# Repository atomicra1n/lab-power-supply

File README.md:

# Lab Power Supply

An adjustable power supply powered by a laptop charger. Features knobs for changing the voltage and current limit, voltage and ampere meter, button to show the current limit on the meter. The circuit is fully analog and features no firmware or microcontroller.

## Features

- Customizable output from 1.25V to about 16.5 volts. 
- Customizable current limit from 0 ampers to about 2.2 ampers.
- Red LED that lights up when the supply is limiting.
- Meter that shows the output voltage and current.
- OUTPUT switch for toggling the outputs.
- SHOW LIMIT button that shows the current limit instead of the voltage on the display.
- Reverse polarity protection.
- Resettable fuse on the input
- Undervoltage lockout
- Runs off a standard 19V laptop charger w/ a 5.5/2.5mm jack.
- Fully THT, no complicated SMD soldering.
- 3D printed enclosure with vents for heat, tilted feet and knobs.

## Motivation

Thinking about what I was going to make for week 5, I wanted something that would be genuinely useful for my future tinkering. Recently, I was reverse engineering a Cisco switch and needed a source of 3.3V. Thankfully, my Raspberry Pi Pico was able to deliver enough, but it was close to not being enough. This would be a good solution for the future!

## Functionality

- The laptop charger plugs into a DC jack on the back of the enclosure. This is wired to a screw terminal on the PCB. Power goes through a resettable fuse and a P-MOSFET for reverse polarity protection.
- An LM2576T-ADJ steps the voltage down. There are two 1k parallel resistors and a 10k potentiometer (VOLTAGE) for the feedback divider.
- A TL431 makes a 2.495 volt reference and one LM324 compares it with a third of the input voltage. If it goes below about 6.8V, the regulator turns off. Above about 8.8V, it turns back on (with hysteresis). This fulfills undervoltage lockout.
- An 0.1 ohm shunt resistor sits in the output's negative path for current sensing. An op-amp amplifies its voltage 11 times.
- A second op-amp compares that with the setting of the CURRENT knob. If the current is too high, current enters the LM2576 feedback pin through the red LED and a 1k resistor, which forces the regulator to lower output. The LED also blocks current from flowing back.
- The SHOW LIMIT button uses a third op-amp to switch the meter's voltage wire between the output and the current limit signal.
- Made only out of 1k/10k resistors to save costs as my local electronics shop has minimum order quantities on each.

## How it was made

All electrical work was done in KiCad and all CAD work was done in Autodesk Fusion. I ran into some issues:

- Originally I planned to use a TL431 to drive the LM2576's ON/OFF pins directly, but the datasheet of the LM2576 says the pin has to go below about 1V to turn it on. However, a TL431 can't get its output below about 2V, so the regulator might never turn on. I switched the LM358 for a LM324 which was even cheaper.
- I had 1k resistor for the green power LED but it is only rated for 7mA, which would come out to about 17 mA at 18V. I added 2 more 1K resistors in series.
- I wired the CURRENT potentiometer backwards which would mean turning it clockwise would lower the limit.
- When routing, I first connected the current sensing input inefficiently which would increase resistance and make the current limit kick in too early.
- The ground pour didn't reach all pads so I needed to add some vias and tracks.
- In Fusion, I often swapped axis and built the tray on the wrong side of the components.

## Tech stack

- KiCad for the schematic and PCB
- Autodesk Fusion for the enclosure and knobs
- JLCPCB for the board, GM Electronic for the parts

## Repo layout

- pcb/ contains all KiCad work, including the project, PCB, footprints and schematic
- pcb/gerbers contains gerber, drill files and a zip file for the gerbers.
- cad/ contains the Fusion files and STEP files
- stl/ contains the printable parts
- images/ contains renders and screenshots

## Bill of materials

| Part | Qty | Source | Unit | Total |
|---|---|---|---|---|
| [PCB Manufacturing (5 pcs)](https://jlcpcb.com) | 1 | JLCPCB | $4.00 | $4.00 |
| [TAEJIN-HTC LM2576T-ADJ regulator](https://www.gme.cz/v/1519044/taejin-htc-korea-lm2576t-adj-vykonovy-spinany-regulatorstep-down) | 1 | GM Electronic | $2.31 | $2.31 |
| [TALEMA DPO-3.0-100 inductor](https://www.gme.cz/v/1494058/talema-dpo-30-100-tlumivka) | 1 | GM Electronic | $3.07 | $3.07 |
| [SB540 Schottky diode](https://www.gme.cz/v/1514436/sb540-yj-schottkyho-dioda) | 2 | GM Electronic | $0.45 | $0.90 |
| [V7143 heatsink](https://www.gme.cz/v/1499787/v7143-black-chladic) | 1 | GM Electronic | $1.56 | $1.56 |
| [Infineon IRF9540N MOSFET](https://www.gme.cz/v/1493222/infineon-irf9540npbf-unipolarni-tranzistor) | 1 | GM Electronic | $0.61 | $0.61 |
| [TL431ACZ reference](https://www.gme.cz/v/1493687/tl431acz) | 1 | GM Electronic | $0.28 | $0.28 |
| [Capacitor 470 microFarad 35V](https://www.gme.cz/v/1486880/hitano-ce-470u-35v-hit-ecr-10x16-rm5-bulk-elektrolyticky-kondenzator) | 5 | GM Electronic | $0.18 | $0.90 |
| [Capacitor 100 nanoFarad](https://www.gme.cz/v/1520318/ck-100n-50v-x7r-rm508-10-keramicky-kondenzator) | 8 | GM Electronic | $0.09 | $0.72 |
| [Resistor 1 kiloohm 0207](https://www.gme.cz/v/1486228/gym-cym-rm-1k-06w-1-0207-metalizovany-rezistor) | 10 | GM Electronic | $0.09 | $0.90 |
| [Resistor 10 kiloohm 0207](https://www.gme.cz/v/1494150/gym-cym-rm-10k-06w-1-0207-metalizovany-rezistor) | 10 | GM Electronic | $0.09 | $0.90 |
| [Shunt resistor 0.1 ohm 3W](https://www.gme.cz/v/1486965/hitano-rd-0r1-3w-5-0617-dratovy-rezistor) | 4 | GM Electronic | $0.22 | $0.88 |
| [Texas Instruments LM324N op-amp](https://www.gme.cz/v/1490186/texas-instruments-lm324n) | 1 | GM Electronic | $0.42 | $0.42 |
| [10 kiloohm potentiometer](https://www.gme.cz/v/1494596/pc1623nbk010-potenciometr) | 2 | GM Electronic | $1.04 | $2.08 |
| [Green LED 3mm](https://www.gme.cz/v/1492964/bright-led-bl-b2141-l-led-3mm-zelena) | 1 | GM Electronic | $0.17 | $0.17 |
| [Red LED 3mm](https://www.gme.cz/v/1492965/bright-led-bl-b5141-l-led-3mm-cervena) | 1 | GM Electronic | $0.17 | $0.17 |
| [KLS7 DPDT push button](https://www.gme.cz/v/1500951/kls-7-p80x80-0-non-lock-tlacitko-do-dps-2-poly-onon) | 1 | GM Electronic | $0.25 | $0.25 |
| [MTS-102-A2 toggle switch](https://www.gme.cz/v/1501004/mts-102-a2-packovy-spinac) | 1 | GM Electronic | $0.66 | $0.66 |
| [DEGSON DG301 screw terminal](https://www.gme.cz/v/1500295/degson-dg301-50-02p-13-00zh-svorkovnice-2pol-roztec-5mm-175a-250v-vstup-90-sroub) | 2 | GM Electronic | $0.15 | $0.30 |
| [Littelfuse RUE300 resettable fuse](https://www.gme.cz/v/1512378/littelfuse-rue300-vratna-pojistka-polyswitch) | 1 | GM Electronic | $0.75 | $0.75 |
| [CA-028-10A volt/amp meter](https://www.gme.cz/v/1518962/creatall-ca-028-10a-digitalni-panelovy-voltmetr-a-ampermetr) | 1 | GM Electronic | $3.73 | $3.73 |
| [DS-026A DC jack 5.5/2.5](https://www.gme.cz/v/1498554/ds-026a-dc-konektor-55-25) | 1 | GM Electronic | $1.04 | $1.04 |
| [M3x10 screw](https://www.gme.cz/v/1511747/wurth-skm3x10-ocelovy-sroub-m3x10mm-phillips-valcova-hlava-pozinkovany) | 5 | GM Electronic | $0.14 | $0.70 |
| [M3 nut](https://www.gme.cz/v/1511808/wurth-skm3k-matice-m3) | 1 | GM Electronic | $0.03 | $0.03 |
| **Parts subtotal** | | | | **$27.33** |
| Shipping (estimate) | | | | $11.00 |
| **Total** | | | | **$38.33** |

I already own the laptop charger so I am not including it. The order quantities are a bit higher somewhere as GM Electronic has minimum order quantities. I will do 3D printing at school. The total exceeds tier 1 so I will cover the rest.

## Printing

- PLA, 0.4mm nozzle, 0.2mm layers, 20% infill
- Tray is printed with the floor on the bed, no supports needed
- Knobs, print the top face on the bed so the shaft hole points up.
- Print 2x foot_12mm and 2x foot_4mm flat side down.

## Assembly

1) Order the PCB from JLCPCB using the gerbers.
2) Some back side parts sit underneath the potentiometers. Solder these first and cut their legs short.
3) Before soldering the SHOW LIMIT button, check it with a multimeter. Make sure the middle pin connects to the outer pin when it's not pressed. If not, rotate the button 180 degrees.
4) Solder the rest of the back side (resistors, capacitors (watch polarity), diodes, TL431, LM324, MOSFET, fuse, inductor, input screw terminal).
5) Screw the LM2576 to the heatsink using the M3 screw and nut, then solder it.
6) Put a piece of electrical tape on the bottom of each potentiometer so its metal tabs can't touch solder joints below it. Then solder the pots, toggle switch, button, LEDs, output terminal on the front side of the PCB.
7) Cut the plugs off the meter's wires and solder them to the 5 meter pads. From pad 1, solder thin red, thin black, thin yellow, thick red, thick black. Check against datasheet/leaflet. Then clip the meter into the cutout.
8) Glue the 12mm feet under the meter side and 4mm feet under the knob side.
9) Mount the DC jack in the back wall of the tray. Drill it bigger if needed. Wire it to the input terminal. Center pin is positive.
10) Put the PCB in the tray and screw it down. Press the knobs onto the potentiometers.

## Usage

1. Plug in the laptop charger, the green POWER LED and meter should be turned on.
2. With OUTPUT off, turn VOLTAGE until the meter shows the desired voltage.
3) Hold SHOW LIMIT and turn CURRENT until the meter shows your desired limit.
4) Connect your circuit and switch OUTPUT on.

## AI disclosure

LLMs (Claude Opus 5.5) were used to plan the concept, get feedback on the schematic/routing, review my work and help find and fix bugs. They were also used for other tedious but simple tasks, like adding the BOM to this README. AI was not used in writing the README, Journal or other parts of the project.

---

Built for [Hack Club Half Life](https://halflife.hackclub.com/) Week 5 (Design Your Own).

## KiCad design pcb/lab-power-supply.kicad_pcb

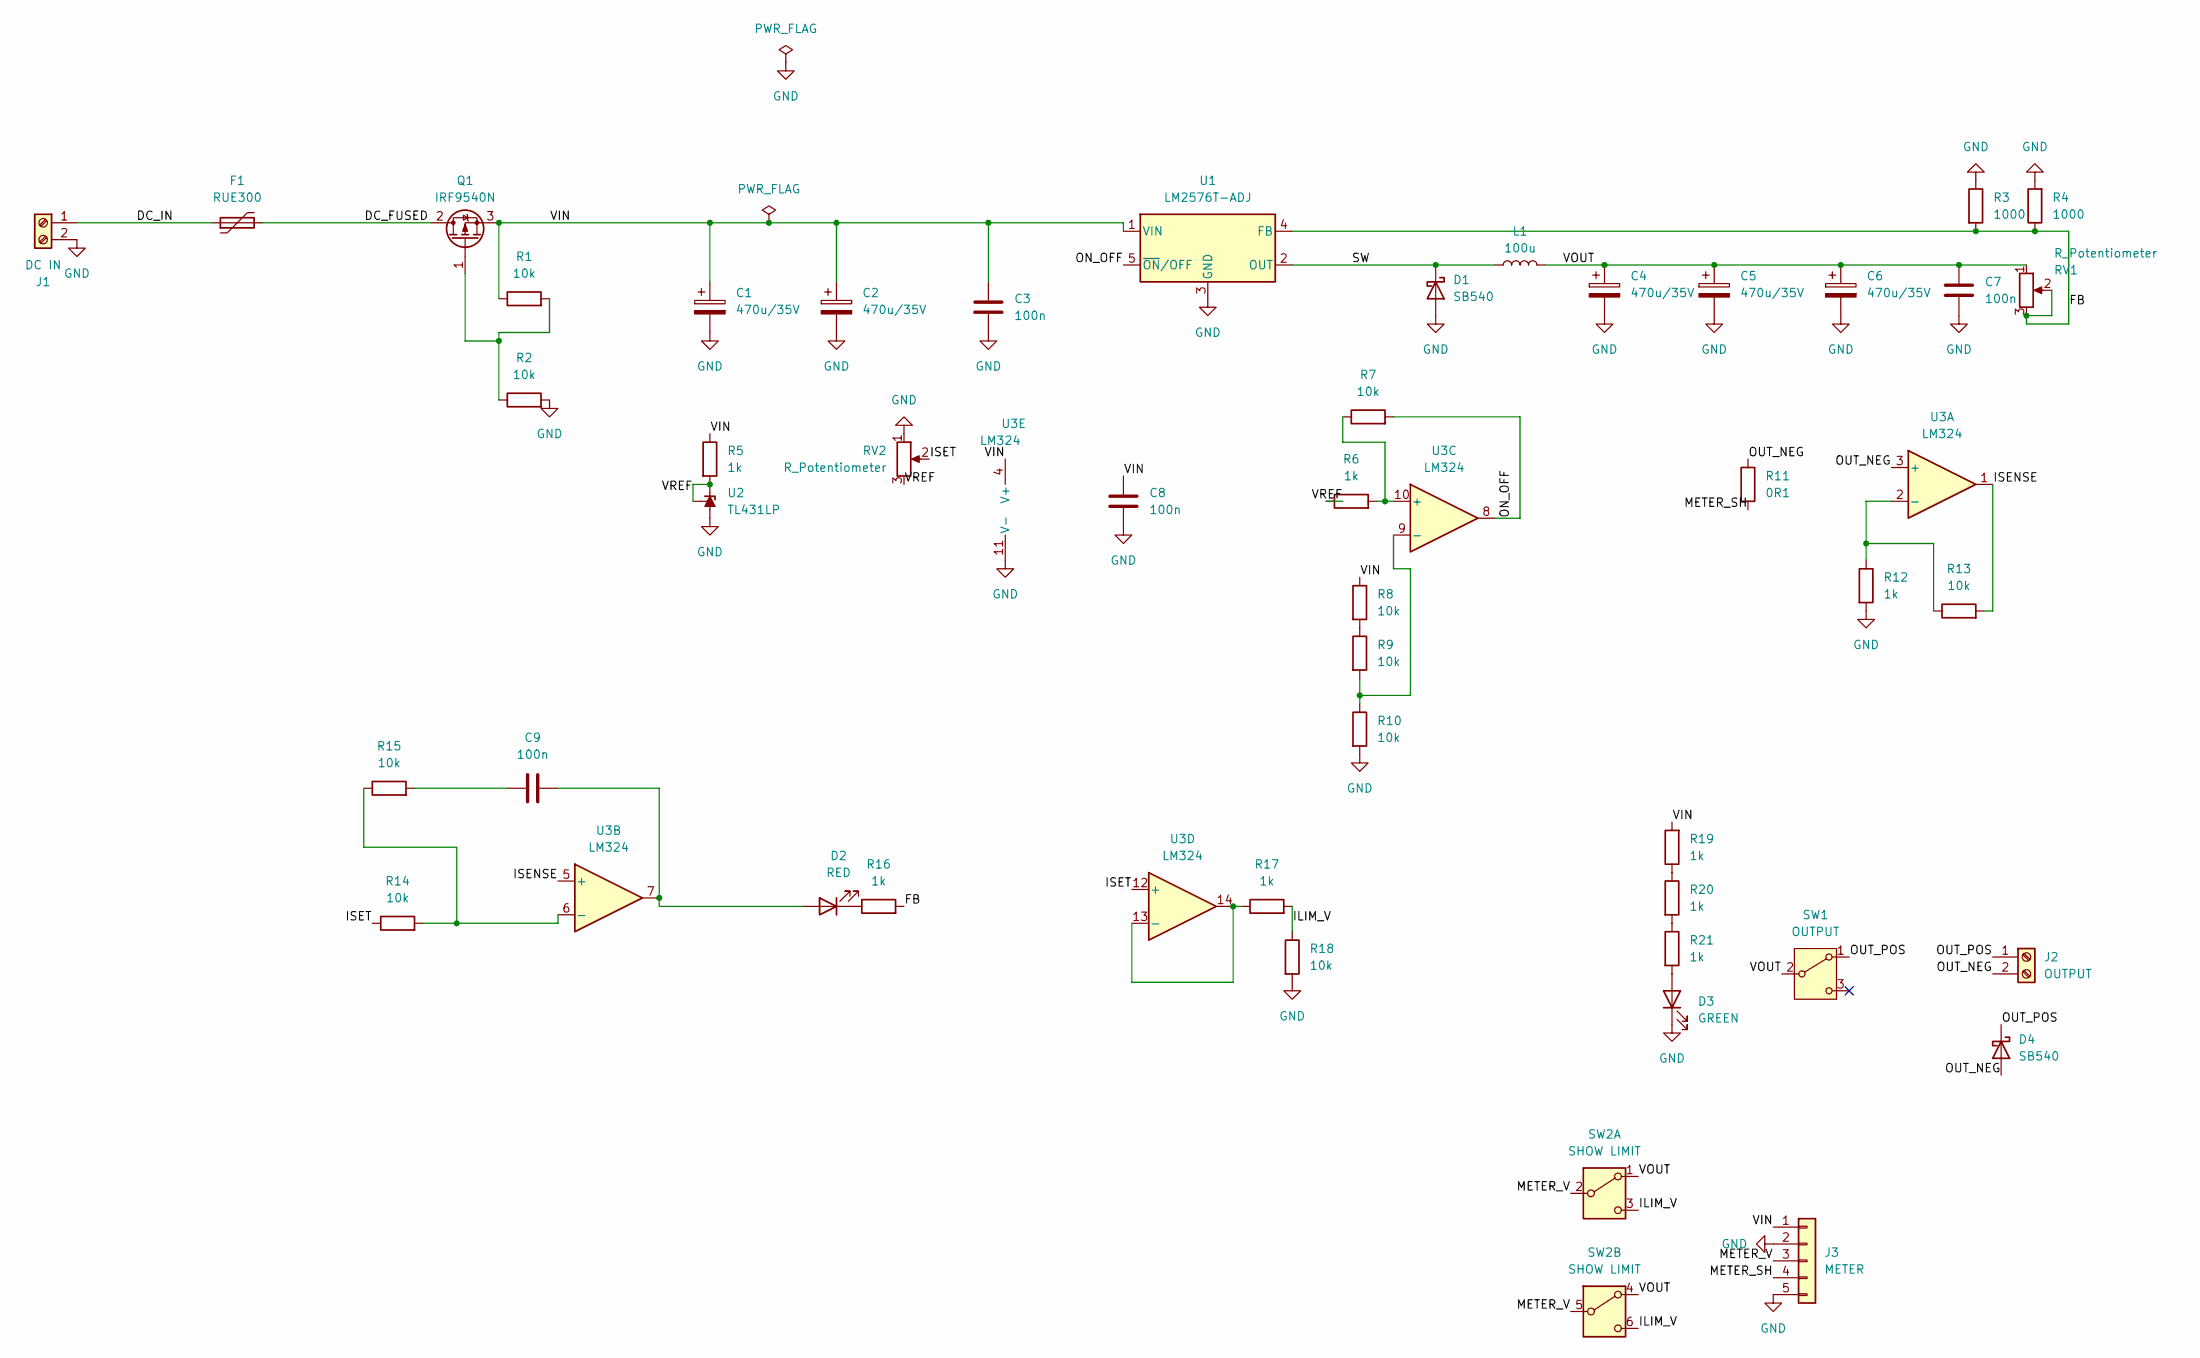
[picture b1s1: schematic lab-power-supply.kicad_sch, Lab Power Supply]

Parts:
C1, C2, C4, C5, C6: 470u/35V; CP_Radial_D10.0mm_P5.00mm
C3, C7, C8, C9: 100n; C_Disc_D5.0mm_W2.5mm_P5.00mm
D1, D4: SB540; D_DO-201AD_P15.24mm_Horizontal
D2: RED; LED_D3.0mm
D3: GREEN; LED_D3.0mm
F1: RUE300; Fuse_Bourns_MF-RG300
J1: DC IN; TerminalBlock_Phoenix_MKDS-1,5-2-5.08_1x02_P5.08mm_Horizont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
J2: OUTPUT; TerminalBlock_Phoenix_MKDS-1,5-2-5.08_1x02_P5.08mm_Horizont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
J3: METER; SolderWire-1sqmm_1x05_P5.4mm_D1.4mm_OD2.7mm
L1: 100u; L_Toroid_Vertical_L26.7mm_W14.0mm_P10.16mm_Pulse_D
Q1: IRF9540N; TO-220-3_Vertical
R1, R2, R7, R8, R9, R10, R13, R14, R15, R18: 10k; R_Axial_DIN0207_L6.3mm_D2.5mm_P10.16mm_Horizontal
R3, R4: 1000; R_Axial_DIN0207_L6.3mm_D2.5mm_P10.16mm_Horizontal
R5, R6, R12, R16, R17, R19, R20, R21: 1k; R_Axial_DIN0207_L6.3mm_D2.5mm_P10.16mm_Horizontal
R11: 0R1; R_Axial_DIN0617_L17.0mm_D6.0mm_P20.32mm_Horizontal
RV1, RV2: R_Potentiometer; Potentiometer_Piher_PC-16_Single_Vertical
SW1: OUTPUT; SW_MTS-102-A2
SW2: SHOW LIMIT; SW_KLS7-P8.0x8.0
U1: LM2576T-ADJ; TO-220-5_Vertical
U2: TL431LP; TO-92_Inline
U3: LM324; DIP-14_W7.62mm_LongPads

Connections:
/DC_FUSED: F1.2, Q1.2 (D)
/DC_IN: F1.1, J1.1
/FB: R3.2, R4.1, R16.2, RV1.2, RV1.3, U1.4 (FB)
/ILIM_V: R17.2, R18.1, SW2.3 (C), SW2.6 (C)
/ISENSE: R13.2, U3.1, U3.5 (+)
/ISET: R14.1, RV2.2, U3.12 (+)
/METER_SH: J3.4, R11.2
/METER_V: J3.3, SW2.2 (B), SW2.5 (B)
/ON_OFF: R7.2, U1.5 (~ON/OFF), U3.8
/OUT_NEG: D4.2 (A), J2.2, R11.1, U3.3 (+)
/OUT_POS: D4.1 (K), J2.1, SW1.1 (A)
/SW: D1.1 (K), L1.1, U1.2 (OUT)
/VIN: C1.1, C2.1, C3.1, C8.1, J3.1, Q1.3 (S), R1.1, R5.1, R8.1, R19.2, U1.1 (VIN), U3.4 (V+)
/VOUT: C4.1, C5.1, C6.1, C7.1, L1.2, RV1.1, SW1.2 (B), SW2.1 (A), SW2.4 (A)
/VREF: R5.2, R6.1, RV2.3, U2.1 (REF), U2.3 (K)
GND: C1.2, C2.2, C3.2, C4.2, C5.2, C6.2, C7.2, C8.2, D1.2 (A), D3.1 (K), J1.2, J3.2, J3.5, R2.2, R3.1, R4.2, R10.2, R12.2, R18.2, RV2.1, U1.3 (GND), U2.2 (A), U3.11 (V-)
unnamed: C9.1, R15.2
unnamed: C9.2, D2.2 (A), U3.7
unnamed: D2.1 (K), R16.1
unnamed: D3.2 (A), R21.2
unnamed: Q1.1 (G), R1.2, R2.1
unnamed: R8.2, R9.1
unnamed: R19.1, R20.1
unnamed: R20.2, R21.1
unnamed: R12.1, R13.1, U3.2 (-)
unnamed: R14.2, R15.1, U3.6 (-)
unnamed: R6.2, R7.1, U3.10 (+)
unnamed: R9.2, R10.1, U3.9 (-)
unnamed: R17.1, U3.13 (-), U3.14

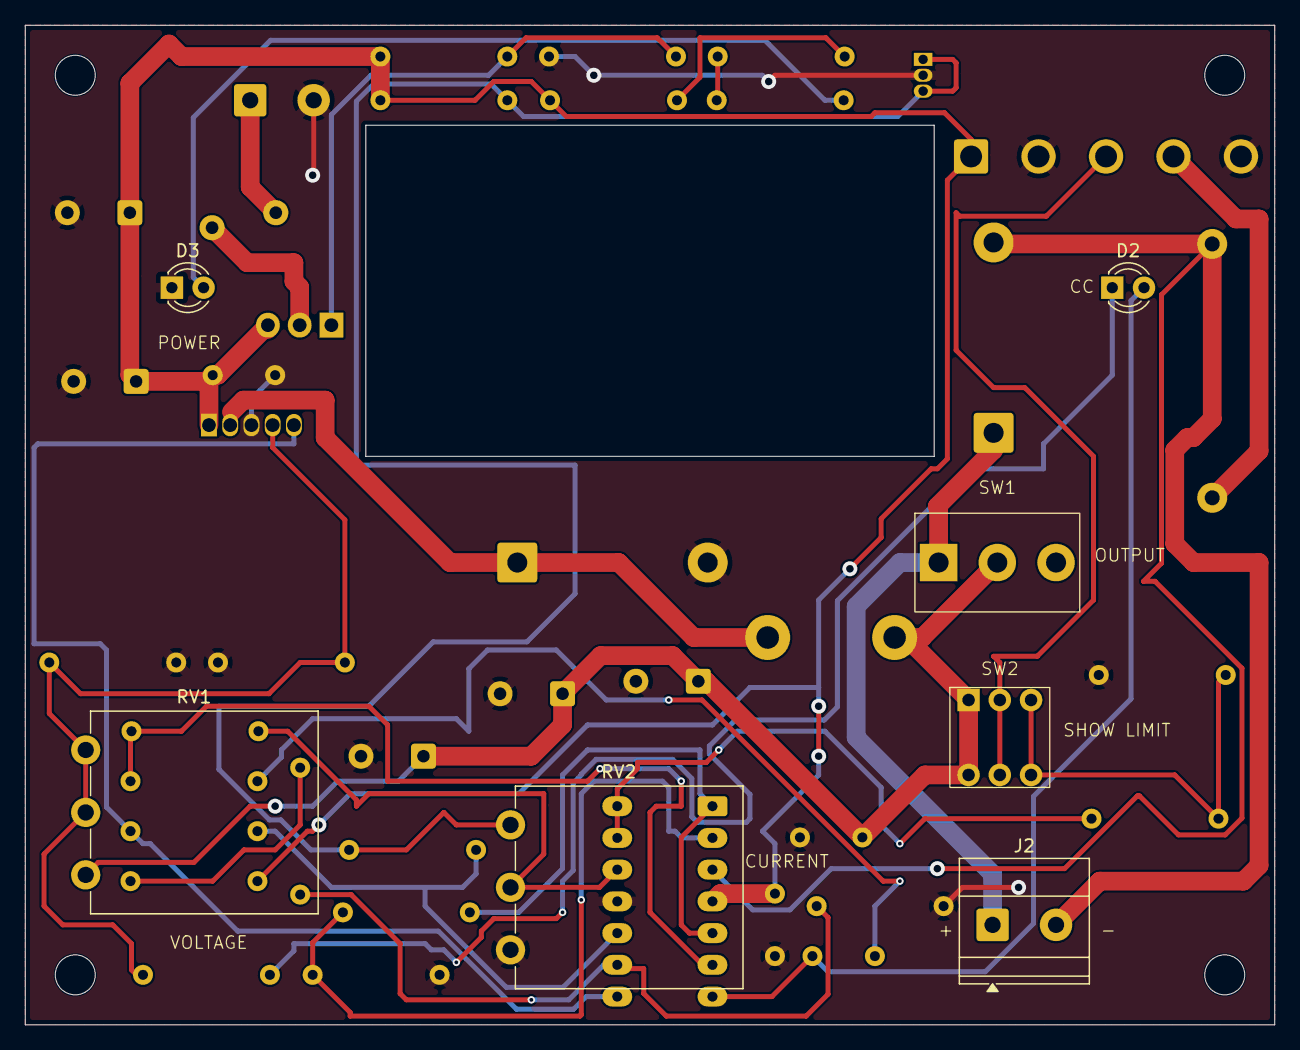
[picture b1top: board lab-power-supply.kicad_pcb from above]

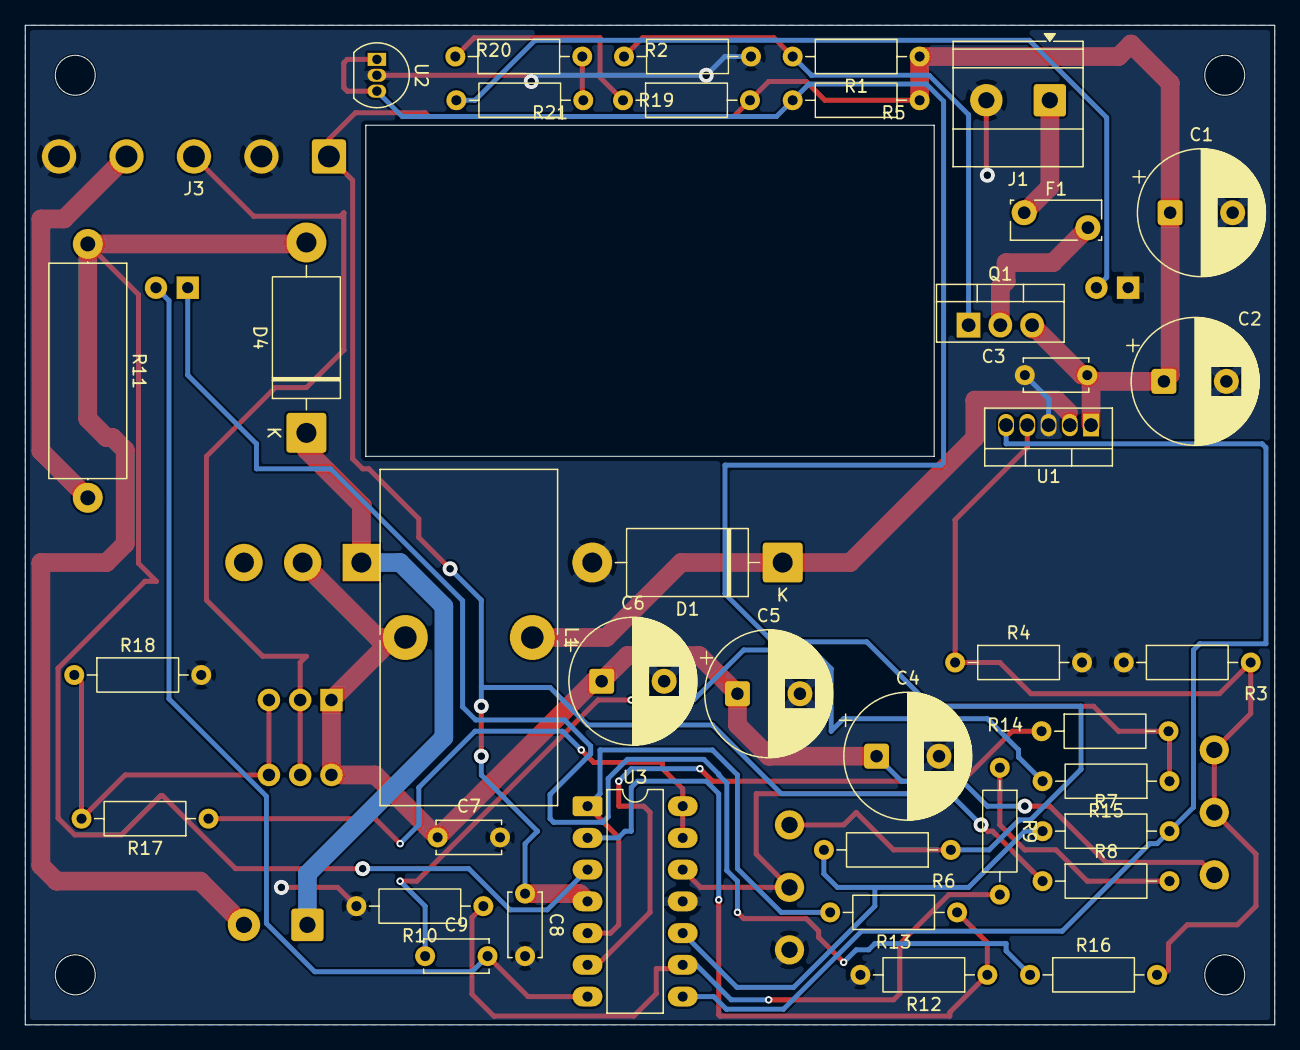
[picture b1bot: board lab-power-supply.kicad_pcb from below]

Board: 2 copper layers, 100.0 x 80.0 mm, 47 parts (40 on the bottom side), 29 nets.
